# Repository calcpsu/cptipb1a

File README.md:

# CalcPack TI BP1A

A Li-Po battery replacement design for TI BP1A battery pack calculators - primarily TI-59. The original batteries had ~ 500mAh capacity (@3.6V: 1.8Wh), while modern Ni-MH replacements are typically ~1500mAh (@3.6V: 5.4Wh).

Li-Po has the advantage of far reduced self-discharge in comparison to Ni-MH, which is an advantage for an intermittently-used device. Even with similar mAh capacity, we can expect longer battery life.

Ni-MH / Ni-CD batteries are notorious for leaking. While Lithium Ion batteries are notorious for self-immolation, a well protected Li-Po battery (particularly in a low current application like this) should be able to be made very safe.

## Features / design goals:
- Direct replacement for a BP1A battery pack
- Compatible with existing charging circuit (although at a slow charge rate)
    - Provides adequate smoothing of rectified AC
    - Provides voltage clamping
- USB charging (when removed from calculator) at faster rate
- Protected from:
    - Overvoltage (USB and pads) at 2x rated voltage and current (IATA requirement)
    - Overcharging (4.2V)
    - Over-discharge (3.1V shutdown, 2.5V cutoff in battery pack)
    - Short circuit and overcurrent (again for IATA requirement)
- Minimum idle/quiescent current to maximise charge time
- Capable of operating TI-59 including card reader
- Similar or higher capacity than typical Ni-MH altenative (1500mAh @ 3.7V [5.55Wh])
  
## License

This work is licensed under a
[Creative Commons Attribution-NonCommercial-ShareAlike 4.0 International License][cc-by-nc-sa].

[![CC BY-NC-SA 4.0][cc-by-nc-sa-image]][cc-by-nc-sa]

[cc-by-nc-sa]: http://creativecommons.org/licenses/by-nc-sa/4.0/
[cc-by-nc-sa-image]: https://licensebuttons.net/l/by-nc-sa/4.0/88x31.png
[cc-by-nc-sa-shield]: https://img.shields.io/badge/License-CC%20BY--NC--SA%204.0-lightgrey.svg

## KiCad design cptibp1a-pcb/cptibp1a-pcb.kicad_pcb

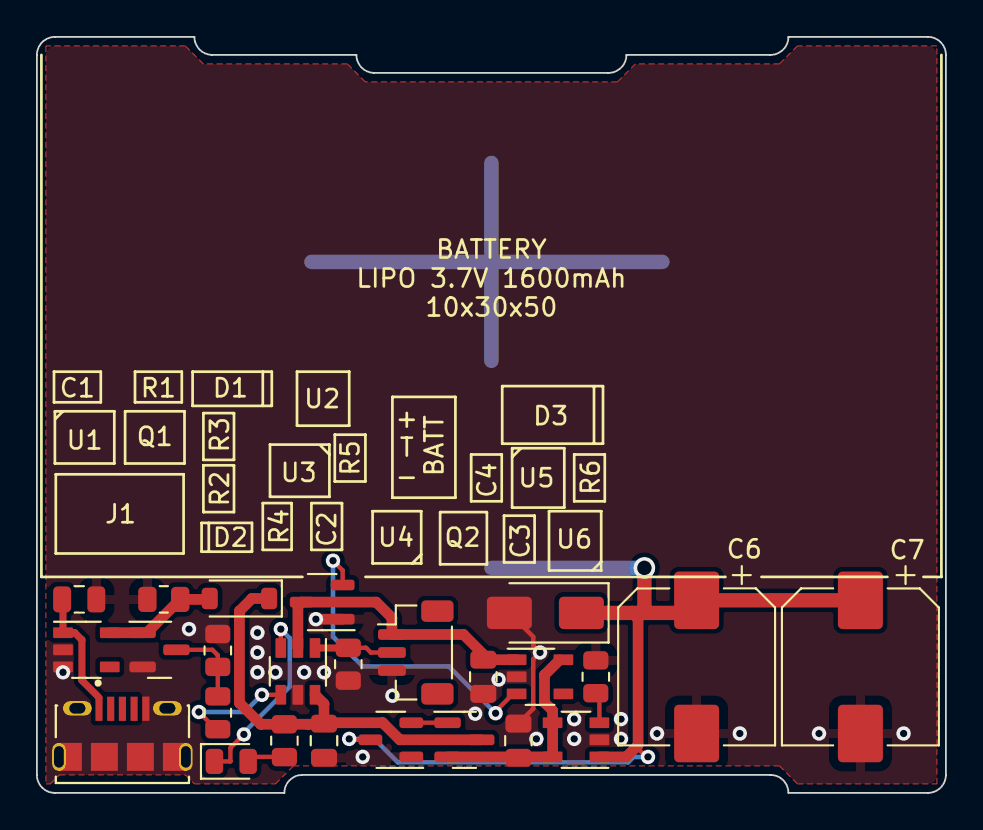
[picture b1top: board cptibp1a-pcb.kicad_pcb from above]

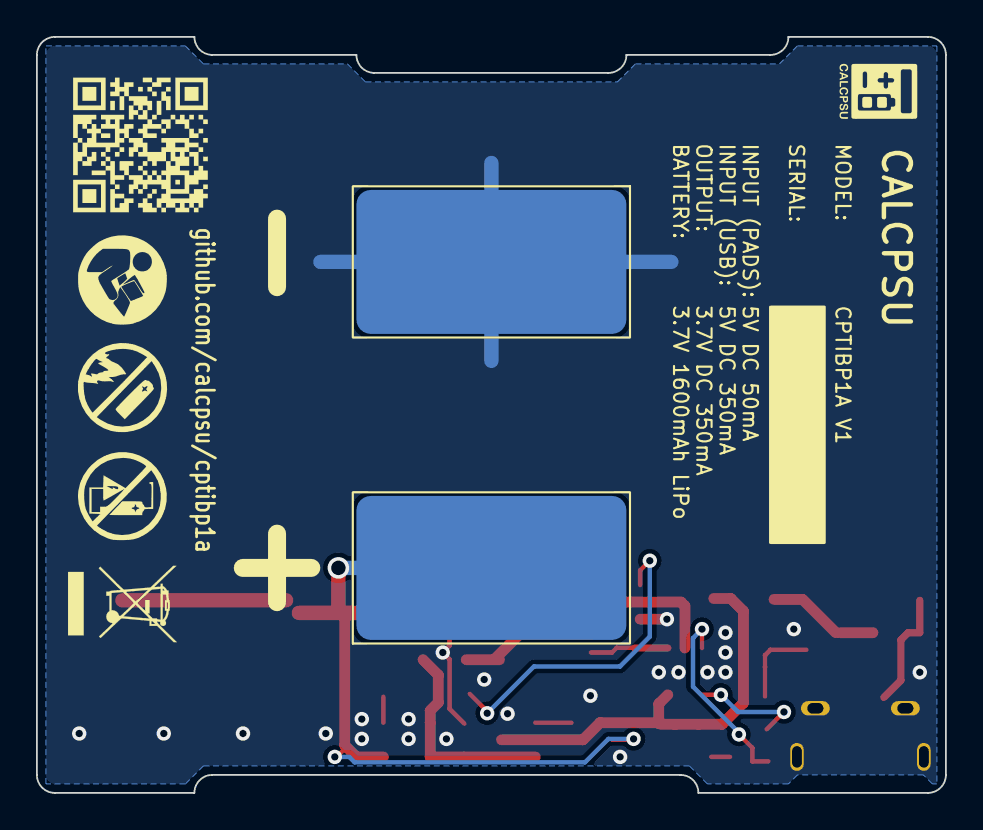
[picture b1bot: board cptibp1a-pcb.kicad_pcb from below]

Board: 2 copper layers, 50.5 x 42.0 mm, 27 parts (2 on the bottom side), 15 nets.

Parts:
BT1: LiPo; JST_SH_BM03B-SRSS-TB_1x03-1MP_P1.00mm_Vertical
C1: 1u; C_0805_2012Metric
C2: 0u1; C_0805_2012Metric
C3, C4: 4u7; C_0805_2012Metric
C6, C7: 1000u/10V; CP_Elec_8x10.5
D1: PMEG40T10ERX; D_SOD-123
D2: RED; LED_0805_2012Metric
D3: 5V6/3W; D_SMA
J1: 10118194-0001LF; AMPHENOL_10118194-0001LF
J2: PAD+; PAD_8x15
J3: PAD-; PAD_8x15
Q1: 2N7002; SOT-23
Q2: AO3413; SOT-23
R1, R5, R6: 10k; R_0805_2012Metric
R2: 1k8; R_0805_2012Metric
R3: 8k6; R_0805_2012Metric
R4: 3k; R_0805_2012Metric
U1: NCP360SNT; SOT-23-5_TI_DBV5
U2: APX809S-31SA; SOT-23-3
U3: BQ21040; SOT-23-6_TI_DBV6
U4: APX810S-44SA; SOT-23-3
U5: MAX40203AUK; SOT-23-5_TI_DBV5
U6: NCP380HSN05; SOT-23-5_TI_DBV5

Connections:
/B+: BT1.1, C4.1, U2.3 (VCC), U3.2 (VOUT), U5.1 (VDD)
/CHG: D2.1 (K), U3.3 (~CHG)
/EN: U2.2 (~RESET), U5.3 (EN)
/G: Q2.1 (G), U4.2 (RESET)
/GND: BT1.3, C1.2, C2.2, C3.2, C4.2, C6.2, C7.2, D3.2 (A), J1.5, J1.S1 (SHIELD), J1.S2 (SHIELD__1), J1.S3 (SHIELD__2), J1.S4 (SHIELD__3), J1.S5 (SHIELD__4), J1.S6 (SHIELD__5), J3.1, Q1.2 (S), R1.1, R3.1, R5.1, R6.1, U1.2 (GND), U1.3 (~EN), U2.1 (GND), U3.5 (GND), U4.1 (GND), U5.2 (GND), U6.2 (GND)
/LCHG: D2.2 (A), R4.1
/PROG: R2.2, U3.4 (ISET)
/PROG2: Q1.3 (D), R2.1, R3.2
/TS: BT1.2, R5.2, U3.1 (TS)
/VBUS: D1.2 (A), Q1.1 (G), R1.2, U1.5 (OUT)
/VBUS1: C1.1, J1.1, U1.1 (IN)
/VCC: C2.1, D1.1 (K), Q2.3 (D), R4.2, U3.6 (VIN)
/VOUT: C3.1, Q2.2 (S), U5.5 (OUT), U6.4 (EN), U6.5 (IN)
/VOUTF: C6.1, C7.1, D3.1 (K), J2.1, U4.3 (VCC), U6.1 (OUT)
unnamed: R6.2, U6.3 (~OC)

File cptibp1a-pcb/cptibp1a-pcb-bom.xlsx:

Id | Designator | Footprint | Quantity | Designation | Supplier and ref | Column1 | _1 | MPN
1 | U1 | SOT-23-5_TI_DBV5 | 1 | NCP360SNT |  |  |  | NCP360SNT1G
2 | F1 | Fuse_1210_3225Metric | 1 | 0ZCJ0050AF2E |  |  |  | 0ZCJ0050AF2E
3 | Q2 | SOT-23 | 1 | AO3413 |  |  |  | AO3413
4 | C6,C7 | CP_Elec_8x10.5 | 2 | 1000u/10V |  |  |  | EEE-FT1A102GP
5 | D2 | LED_0805_2012Metric | 1 | RED |  |  |  | B1701USD-20D000114U1930
6 | Q1 | SOT-23 | 1 | 2N7002 |  |  |  | DMG2302U-7
7 | C4 | C_0805_2012Metric | 1 | 4u7 |  |  |  | CL21A475KAQNNNE
8 | R2 | R_0805_2012Metric | 1 | 1k8
9 | R4 | R_0805_2012Metric | 1 | 3k |  |  |  | RC0805FR-073KL
10 | R5,R1 | R_0805_2012Metric | 2 | 10k |  |  |  | RC0805FR-0710KL
11 | C1 | C_0805_2012Metric | 1 | 1u |  |  |  | CL21B105KAFNNNE
12 | U5 | SOT-23-5_TI_DBV5 | 1 | MAX40203AUK |  |  |  | MAX40203AUK+T
13 | U3 | SOT-23-6_TI_DBV6 | 1 | BQ21040 |  |  |  | BQ21040DBVR
14 | D1 | D_SOD-123 | 1 | PMEG40T10ERX |  |  |  | PMEG40T10ERX
15 | J1 | AMPHENOL_10118194-0001LF | 1 | 10118194-0001LF |  |  |  | 10118194-0001LF
16 | C2 | C_0805_2012Metric | 1 | 10u |  |  |  | CL21A106KAYNNNE
17 | BT1 | JST_SH_BM03B-SRSS-TB_1x03-1MP_P1.00mm_Vertical | 1 | LiPo |  |  |  | BM03B-SRSS-TB
18 | U2 | SOT-23-3 | 1 | APX809S-31SA |  |  |  | APX809S-31SA-7
19 | R3 | R_0805_2012Metric | 1 | 8k66 |  |  |  | RC0805FR-078K66L
20 | U4 | SOT-23-3 | 1 | APX810S-44SA |  |  |  | APX810S-44SA
21 | D3 | D_SMA | 1 | 5V6/3W |  |  |  | 3SMAJ5919B-TP
22 | J3 | PAD_6x15 | 1 | PAD-
23 | J2 | PAD_6x15 | 1 | PAD+

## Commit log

2024-03-05 cleanup
2024-03-23 rev1
2024-04-16 Rev1 update (minor)
2024-04-16 Move power connector (battery clash reduce)
2024-04-17 remove nonpop
2024-04-24 Add sim
